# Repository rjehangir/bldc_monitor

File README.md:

BLDC Monitor
========

The BLDC Monitor is an Arduino compatible board with voltage, current, and RPM sensors for a three-phase brushless motor. The board has components to monitor two motors simultaneously. The software is written in C++ and communicates with a Python program through serial. An ncurses interface allows the motor to be controlled with the arrow keys on the keyboard. Data is displayed in the terminal and also plotted live through Plot.ly.

##Features

* Atmega328p microcontroller
* RPM sensor that uses motor wire for input. An optoisolator protects the rest of the circuit and an active low-pass filter removes high frequency PWM and converts the EMF wave to a binary signal.
* Allegro hall effect current sensors for accurate current measurements
* Measures 2 motors simultaneously

##Interface

The interface is written in Python. It uses the curses, crcmod, serial, and plotly libraries. To run the interface:

```bash
./bldc_monitor.py -p [serial port] -o [csv file to write (optional)]
```

##Releases

TBD

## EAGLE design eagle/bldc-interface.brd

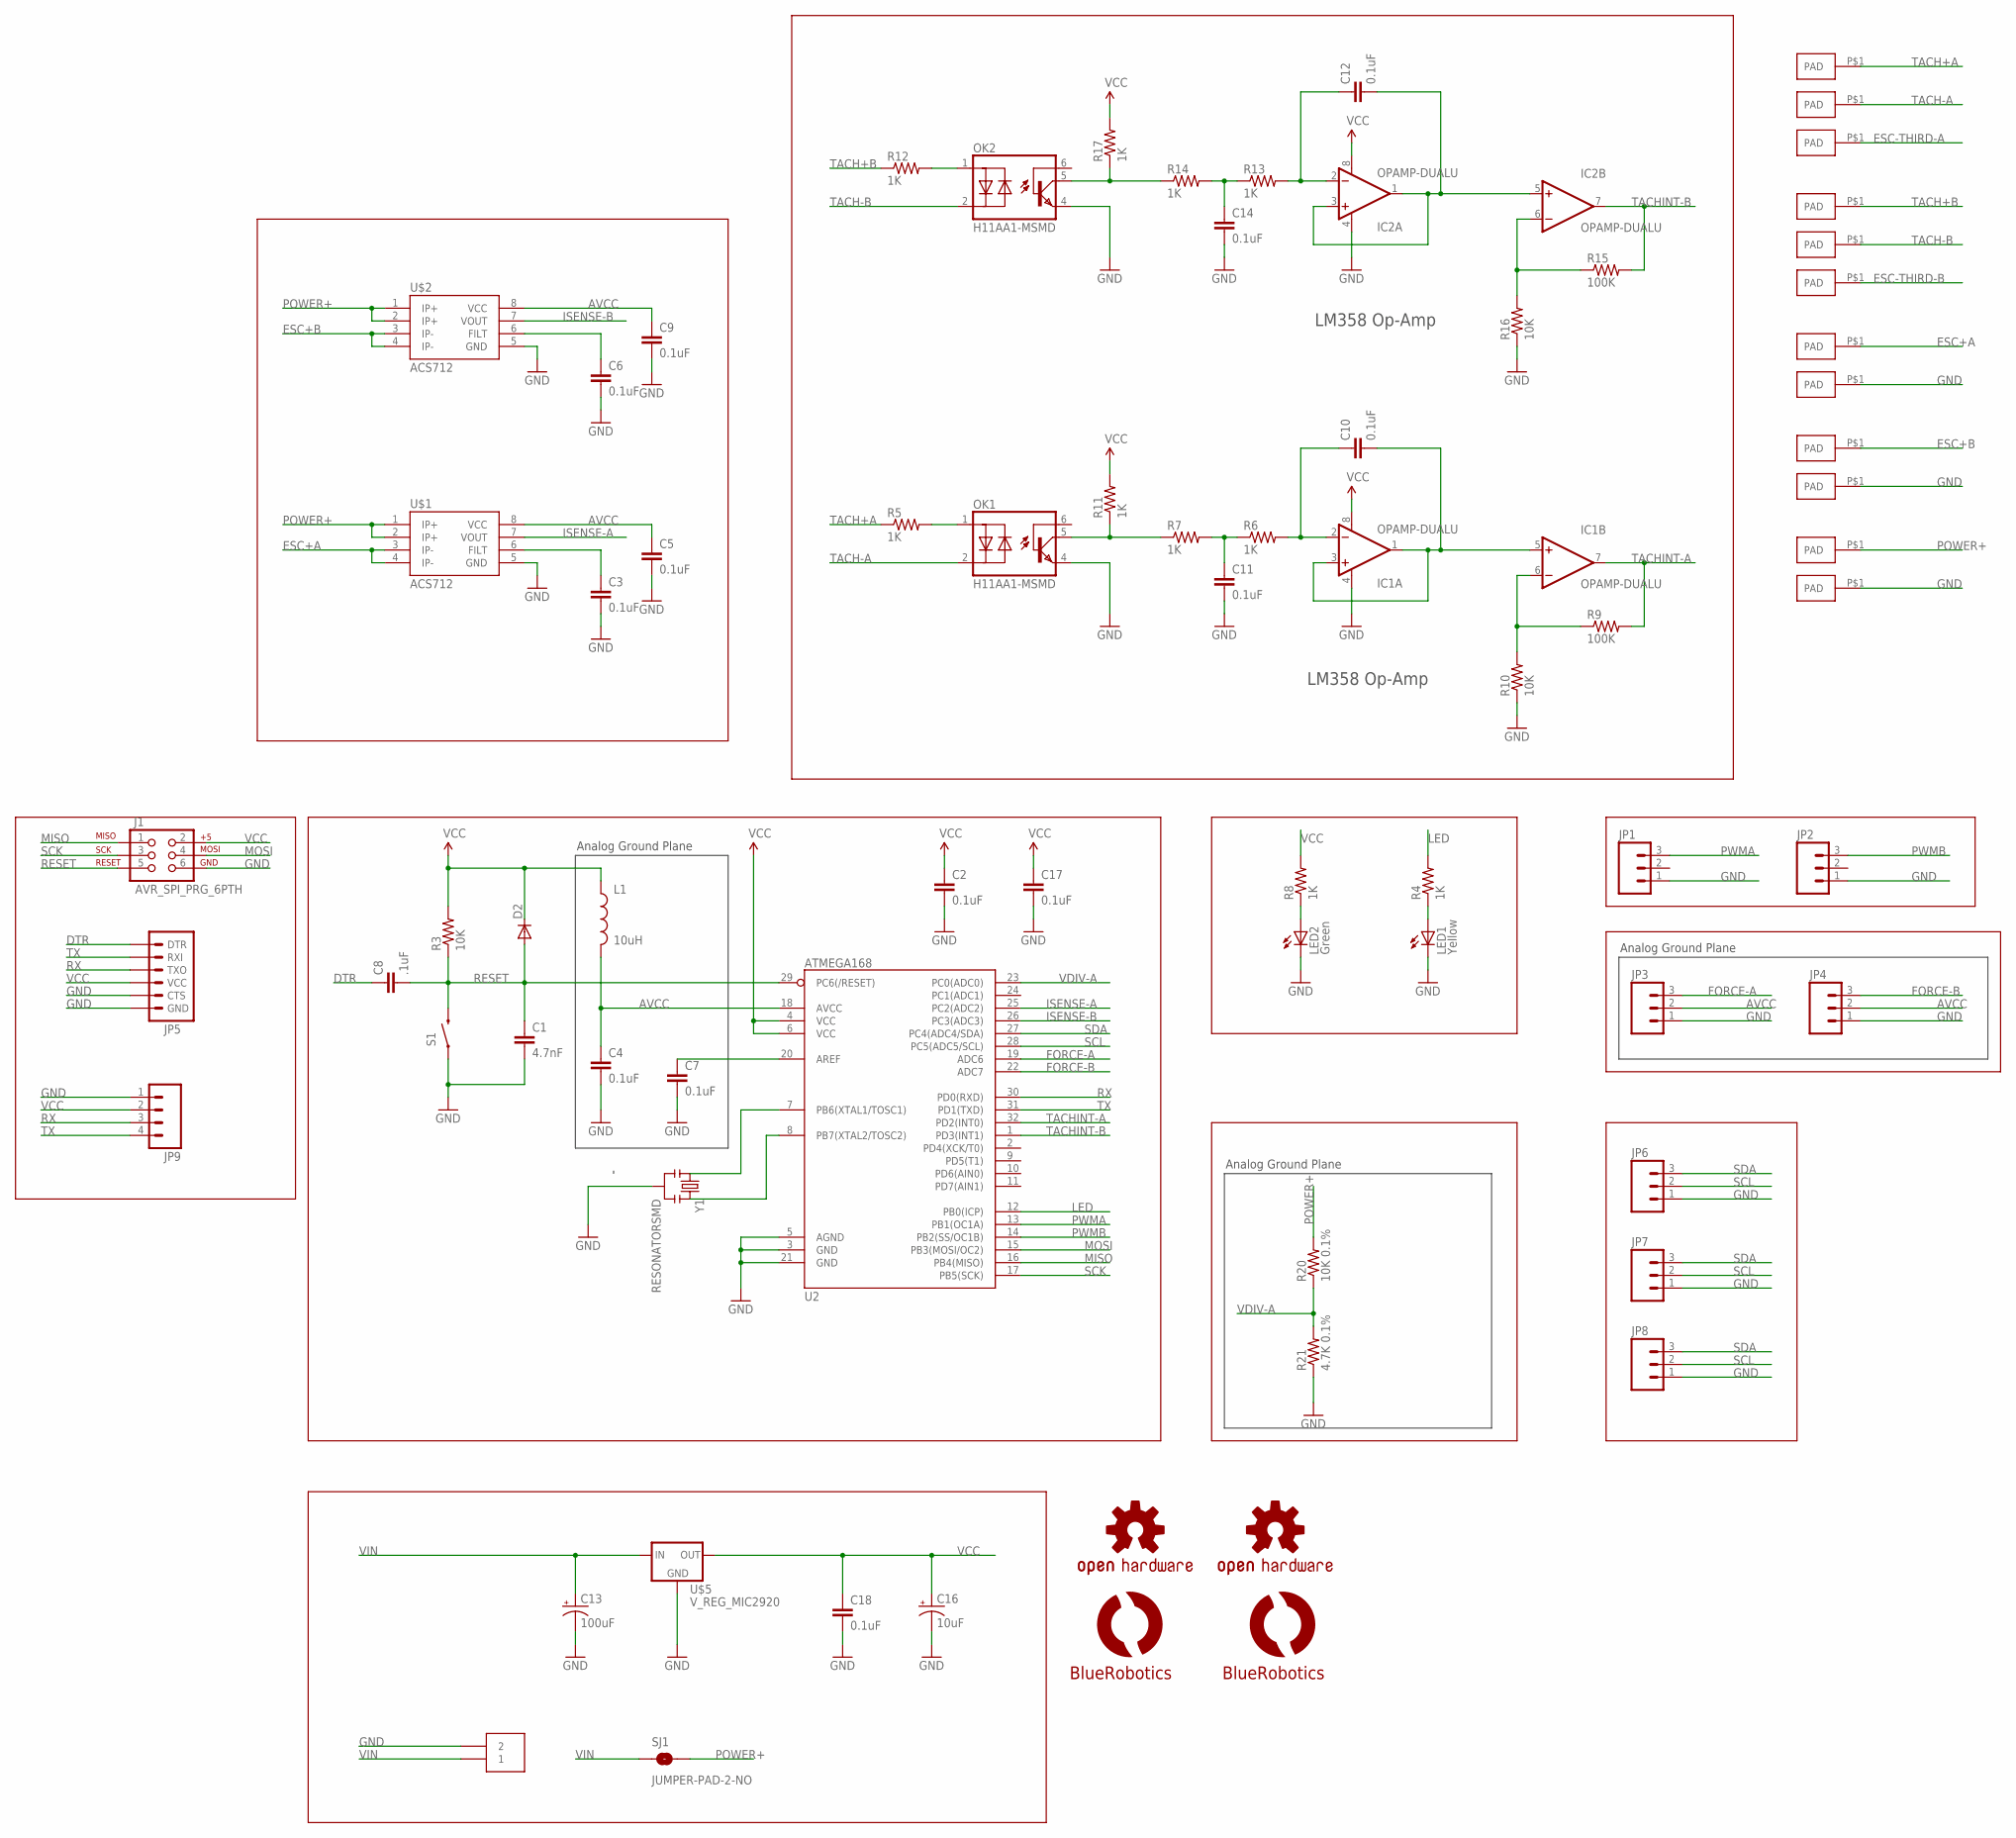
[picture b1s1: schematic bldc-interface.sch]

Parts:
C1: 4.7nF; 0603-CAP
C2, C3, C4, C5, C6, C7, C9, C10, C11, C12, C14, C17, C18: 0.1uF; 0603-CAP
C8: .1uF; 0603-CAP
C13: 100uF; CPOL-RADIAL-100UF-25V
C16: 10uF; EIA3216
D2: DIODESOD; SOD-323
IC1, IC2: OPAMP-DUALU; SO08
J1: AVR_SPI_PRG_6PTH; 2X3
JP1, JP2, JP3, JP4, JP6, JP7, JP8: M03PTH; 1X03
JP5: ARDUINO_SERIAL_PROGRAMPTH; 1X06
JP9: M04PTH; 1X04
L1: 10uH; 0603
LED1: Yellow; LED-0603
LED2: Green; LED-0603
LOGO1: OSHW-LOGOS; OSHW-LOGO-S
LOGO2: OSHW-LOGOM; OSHW-LOGO-M
OK1, OK2: H11AA1-MSMD; DIL6-SMD
R3, R10, R16: 10K; 0603-RES
R4, R6, R7, R8, R11, R13, R14, R17: 1K; 0603-RES
R5, R12: 1K; R2512
R9, R15: 100K; 0603-RES
R20: 10K 0.1%; 0603-RES
R21: 4.7K 0.1%; 0603-RES
S1: reset; TACTILE_SWITCH_SMD
SJ1: JUMPER-PAD-2-NO; PAD-JUMPER-2-NO_NO_SILK
U2: ATMEGA168; TQFP32-08
U$1, U$2: ACS712; SO08
U$3: TERMINAL-25MM-WEID; LSF-SMT-5MM-2
U$4, U$6, U$7, U$8, U$9, U$10, U$11, U$12, U$13, U$14, U$15, U$16: PADLARGE-ONE-SIDE; PAD-0.2X0.3-ONE-SIDE
U$5: V_REG_MIC2920; SOT223
U$17: LOGOBR-LOGO-M; BR-LOGO-MEDIUM
U$18: LOGOBR-LOGO-S; BR-LOGO-SMALL
Y1: RESONATORSMD; RESONATOR-SMD

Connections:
AVCC: C4.1, C5.1, C9.1, JP3.2, JP4.2, L1.2, U2.18 (AVCC), U$1.8 (VCC), U$2.8 (VCC)
DTR: C8.1, JP5.1 (DTR)
ESC+A: U$1.3 (IP-), U$1.4 (IP-), U$13.P$1
ESC+B: U$2.3 (IP-), U$2.4 (IP-), U$15.P$1
ESC-THIRD-A: U$9.P$1
ESC-THIRD-B: U$12.P$1
FORCE-A: JP3.3, U2.19 (ADC6)
FORCE-B: JP4.3, U2.22 (ADC7)
GND: C1.2, C2.2, C3.2, C4.2, C5.2, C6.2, C7.2, C9.2, C11.2, C13.2 (-), C14.2, C16.C (-), C17.2, C18.2, IC1.4 (V-), IC2.4 (V-), J1.6, JP1.1, JP2.1, JP3.1, JP4.1, JP5.5 (CTS), JP5.6 (GND), JP6.1, JP7.1, JP8.1, JP9.1, LED1.C, LED2.C, OK1.4 (EMI), OK2.4 (EMI), R10.1, R16.1, R21.1, S1.1, U2.3 (GND), U2.5 (AGND), U2.21 (GND), U$1.5 (GND), U$2.5 (GND), U$3.2, U$3.4 (2), U$5.2 (GND), U$8.P$1, U$14.P$1, U$16.P$1, Y1.2
ISENSE-A: U2.25 (PC2(ADC2)), U$1.7 (VOUT)
ISENSE-B: U2.26 (PC3(ADC3)), U$2.7 (VOUT)
LED: R4.2, U2.12 (PB0(ICP))
MISO: J1.1, U2.16 (PB4(MISO))
MOSI: J1.4, U2.15 (PB3(MOSI/OC2))
unnamed: C6.1, U$2.6 (FILT)
unnamed: C3.1, U$1.6 (FILT)
unnamed: LED1.A, R4.1
unnamed: C10.1, IC1.2 (-IN), R6.2
unnamed: C10.2, IC1.1 (OUT), IC1.3 (+IN), IC1.5 (+IN)
unnamed: IC1.6 (-IN), R9.1, R10.2
unnamed: C11.1, R6.1, R7.2
unnamed: C7.1, U2.20 (AREF)
unnamed: U2.7 (PB6(XTAL1/TOSC1)), Y1.1
unnamed: U2.8 (PB7(XTAL2/TOSC2)), Y1.3
unnamed: OK1.5 (COL), R7.1, R11.1
unnamed: C12.1, IC2.2 (-IN), R13.2
unnamed: OK1.1 (A), R5.2
unnamed: C12.2, IC2.1 (OUT), IC2.3 (+IN), IC2.5 (+IN)
unnamed: LED2.A, R8.1
unnamed: C14.1, R13.1, R14.2
unnamed: IC2.6 (-IN), R15.1, R16.2
unnamed: OK2.1 (A), R12.2
unnamed: OK2.5 (COL), R14.1, R17.1
POWER+: R20.2, SJ1.2, U$1.1 (IP+), U$1.2 (IP+), U$2.1 (IP+), U$2.2 (IP+), U$7.P$1
PWMA: JP1.3, U2.13 (PB1(OC1A))
PWMB: JP2.3, U2.14 (PB2(SS/OC1B))
RESET: C1.1, C8.2, D2.2 (A), J1.5, R3.1, S1.3 (2), U2.29 (PC6(/RESET))
RX: JP5.3 (TXO), JP9.3, U2.30 (PD0(RXD))
SCK: J1.3, U2.17 (PB5(SCK))
SCL: JP6.2, JP7.2, JP8.2, U2.28 (PC5(ADC5/SCL))
SDA: JP6.3, JP7.3, JP8.3, U2.27 (PC4(ADC4/SDA))
TACH+A: R5.1, U$6.P$1
TACH+B: R12.1, U$10.P$1
TACH-A: OK1.2 (C), U$4.P$1
TACH-B: OK2.2 (C), U$11.P$1
TACHINT-A: IC1.7 (OUT), R9.2, U2.32 (PD2(INT0))
TACHINT-B: IC2.7 (OUT), R15.2, U2.1 (PD3(INT1))
TX: JP5.2 (RXI), JP9.4, U2.31 (PD1(TXD))
VCC: C2.1, C16.A (+), C17.1, C18.1, D2.1 (C), IC1.8 (V+), IC2.8 (V+), J1.2, JP5.4 (VCC), JP9.2, L1.1, R3.2, R8.2, R11.2, R17.2, U2.4 (VCC), U2.6 (VCC), U$5.3 (OUT)
VDIV-A: R20.1, R21.2, U2.23 (PC0(ADC0))
VIN: C13.1 (+), SJ1.1, U$3.1, U$3.3 (1), U$5.1 (IN)

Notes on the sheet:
Analog Ground Plane
LM358 Op-Amp

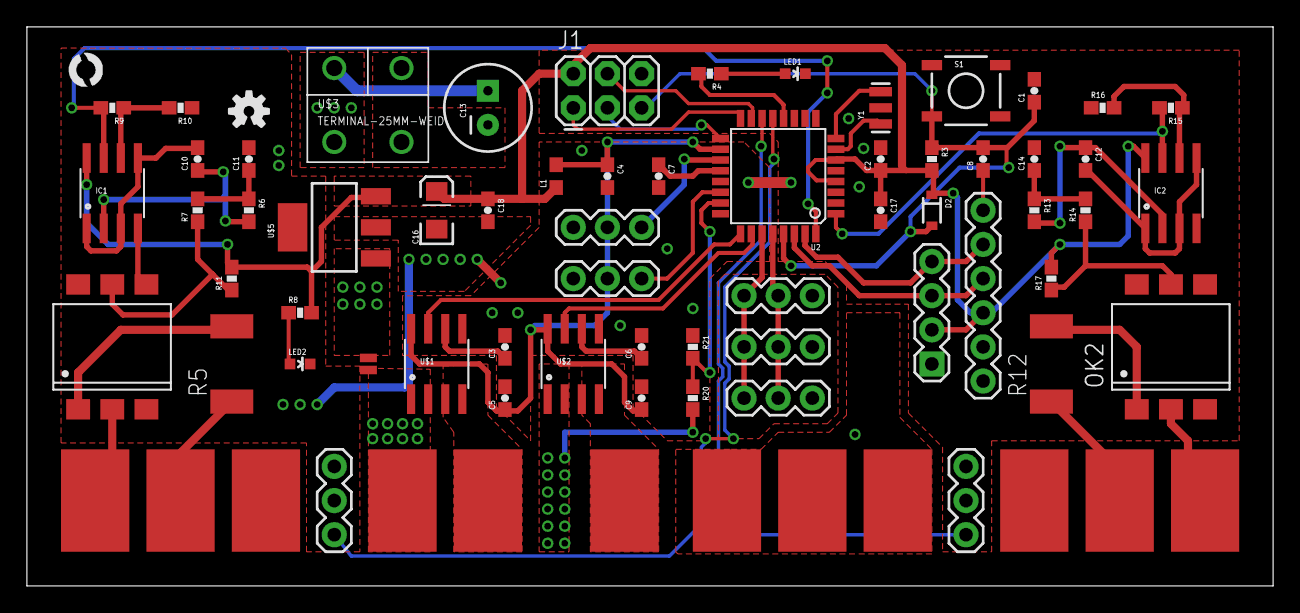
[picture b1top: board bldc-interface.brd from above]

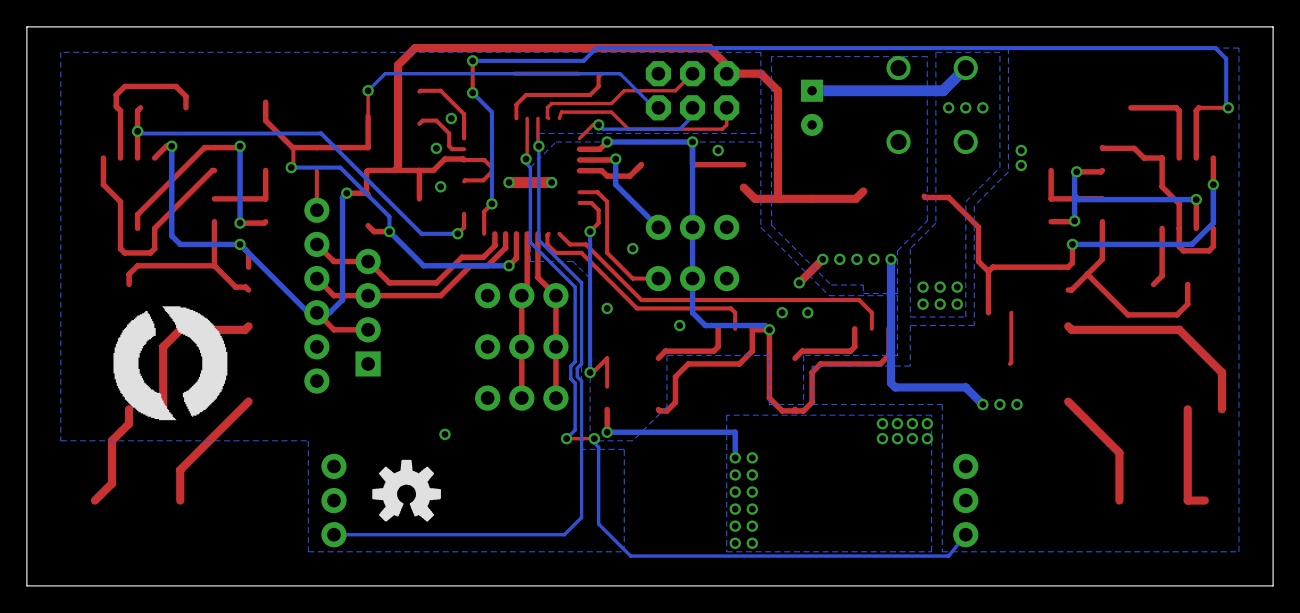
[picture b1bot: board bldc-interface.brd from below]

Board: 2 copper layers, 92.7 x 41.6 mm, 76 parts (2 on the bottom side), 49 nets.

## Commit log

2013-12-06 Added basic files. No work has really been done yet but the directory structure is set up. The entire repository is structure to allow the entire folder to be copied into the Arduino "libraries" dire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
2013-12-06 Restructured files slightly so that the directory could be copied into the Arduino libraries folder easily.
2013-12-06 Removed old files.
2013-12-07 Added basic Python script that opens a PyQtGraph window and plots data. The serial functionality has not yet been added so there is a function that returns a random value to simulate serial data.
2013-12-07 Added function definitions to the plotuino namespace to allow messages to be sent in the proper format. A preamble is used for synchronization and a CRC16 checksum used for data validation. An exampl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
2013-12-09 After getting a single basic plot to work, I added three other plots and labeled them for voltage, current, power, and rpm. This will eventually be done dynamically but it is hardcoded for now. The x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
2013-12-09 Added a text box in the upper right corner of each plot to display the current value of the data. The text item is a little jumpy because PyQtGraph only allows TextItems to be positioned relative to 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
2013-12-09 Tested the code with an Arduino outputting serial data. It works correctly although the handling of a failed checksum in less than great. The program defaults to using the "fake" serial port that gen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
2013-12-11 Added several lines to the PDE file during testing. The serial connection has beeen tested and works properly.
2013-12-11 Copied plotuinoAnalog sketch to plotuinoBLDC, which will measure voltage, current, RPM, and force generated by a brushless motor. The data will be plotted for analysis.
2013-12-11 Added a voltage measuring function for the BLDC measuring tool. It is well documented and should be fairly easy to modify if a different voltage divider, ADC, or filter is used.
2013-12-11 Fixed two "no return statement in non-void function" errors so that it compiles properly.
2013-12-11 Change the low pass filter in the voltage measuring function to recalculate alpha at every loop so as to avoid instability caused by variable loop periods.
2013-12-11 Finished adding the voltage, current, and rpm measurement functions. The main loop is also complete. Measurements are made at 200 Hz and output is sent at 10 Hz. These values are arbitrary and can be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
2013-12-11 Added center offset for current sensor, which is a plus/minus sensor. This was missing before.
2013-12-13 Tested the embedded code with the Python code and fixed a few bugs. It is working now and the voltage/current/power/RPM example is functioning.
2013-12-15 Adjusted the hard-coded value for the center of the analog current sensor to match empirical value.
2014-01-11 Added RPM/V (Kv) to the BLDC example and the plotuino file. Remember, eventually the plotuino.py file will be generic and configured through the Arduino communication.
2014-02-05 Added a thrust plot and appropriate data field to the Arduino code.
2014-02-21 Added the necessary functions to measure thrust with the FC22 0-25 lb force sensor. There is still no factor for the moment arm, but that will be added shortly.
2014-02-21 Added a factor to account for different distance from the pivot point. The FORCE_RATIO is multiplied by the measured force to get the actual thrust force.
2014-04-09 Added Plotly example and basic plotlyuino. It does not work yet.
2014-04-09 Finally got the plotting working and got multiple streaming plots working in in test_plotly3.py. Once I get timestamps working correctly it can be integrated with the python serial code.
2014-04-10 Finished test_plotly3.py, which now streams four plots simultaneously. This is ready to be integrated with the python code for serial communication.
2014-04-25 Integrated working plotly code with plotuino.py code and it seems to be working well. Haven't tested it with the actual Arduino yet.
2014-04-25 Updated Arduino output to match the Plotly plot output. The old plots need to be updated to reflect this as well.
2014-04-26 Fixed a few constants.
2014-04-26 Tested the code with electronics streaming to Plotly. It is working great!
2014-04-27 Added curses to the plotlyuino code to allow the motor to be controlled from Arduino. Also added the needed code to the Arduino. It reads in a byte that is incremented with the arrow or pg up/down ke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
2014-04-27 Fixed the low pass filters on the arduino code.
2014-04-28 Quick fix to allow operation without an active serial port
2014-04-29 Improved the curses display so that the test stand could be used even if plotly is not working.
2014-04-29 Added a little more info to the ncurses display including data type (simulated vs. serial) and number of stream points sent to Plotly. I wish Plotly had some feedback status information I could print.
2014-04-29 Changed precision of several values being printed in the curses display for ease of reading
2014-04-30 Misc changes
2014-04-30 Put serial reading and sending to plotly in separate timing loops so that the serial data can be read at a high rate to absorb and freezing and the plotly data can be appropriately throttled.
2014-05-01 Added a line to close the serial port on quit.
2014-05-01 Added a try/except block to catch broken pipe IOErrors. I'm not sure what is causing them, but there will be a 5 second timeout and then a reattempt.
2014-06-03 Updated code for new plotly python API
2014-06-08 Added an hour meter functionality that counts the time the passes and stores it constantly to a file as a json readable object. When the program is restarted, it reads the value from the file and con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
2014-06-09 Added much more functionality to the cumulative hour meter. It now also logs time x RPM and time x thrust to provide average values of each. It also only logs when the RPM is greater than zero.
2014-06-09 Fixed a few bugs in the cumulative time meter.
2014-06-20 Creates a new hourmeter log if the current one cannot be read properly.
2014-06-21 Modified the code for the BR BLDC monitor board and for the Afro ESC which can run in both directions.
2014-06-21 Restructured the project. It is no longer an attempt to make a generic Arduino plotting tool but to make a BLDC monitoring tool. That had already happened but now it is official. I deleted all files 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
2014-06-22 Updated to work with INT0 instead of INT1 since that pin is being used on the BLDC monitor board for motor A. Note that none of the motor B sensors have been added to software yet. Everything is work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
2014-06-23 Fixed error in the current sensor that would cause the current to appear higher than it actually was.
2014-07-01 Modified the analog measurement code to first measure the value of Vcc compared to the internal 1.1V reference. This value is then used in all the other ADC measurements to provide a more accurate va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
2014-07-01 Added defines for the min and max pulse widths sent to the ESC.
2014-07-01 Fixed typo.
2014-07-08 Added switch statement for different output types and added a blank for the EasyTransfer library method. Still need to add the struct for that library and the actual methods.
2014-07-16 Removed dependency on EasyTransfer library which will be replaced with my 'Transfer' library.
2014-07-18 Added CMakeLists file.
2014-07-18 Added Transfer class and the needed functions to send the bldc data as a c struct over serial. Should also add this to the python program and do away with the 'comm.*' files.
2014-07-18 Added motor B to the bldc_monitor. This hasn't been tested yet, but theoretically it should be able to monitor and output data for two motors simultaneously.
2014-07-29 Changed script to read from Transfer.
2014-07-29 Receiving data in Transfer format is now working.
2014-07-29 Changes to send commands via Transfer.
2014-07-29 Not fully tested, but sending should now be accomplished with Transfer.
2014-08-05 Changes made quickly on RasPi.
2014-08-22 Small changes.
2014-09-12 Minor changes to the monitor. Having issues sending commands in a timely manner.
2014-09-25 Fixed some stupid mistakes that must have crept in a while ago. RPM measurement is working correctly now.
2014-09-27 Added Eagle files for the BLDC monitor, rev1.
2014-09-27 Update README.md
    Updated the README.
2014-10-28 Added the Phant bridge to send data to data.sparkfun.com.
2014-10-28 Added timeout for sending data.
2014-12-01 Added control with potentiometer for use on a vehicle.
2014-12-03 Updates for potentiometer input.

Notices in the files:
parts and their libraries:
SparkFun-AnalogIC: Licensing:Creative Commons ShareAlike 4.0 International - https://creativecommons.org/licenses/by-sa/4.0
